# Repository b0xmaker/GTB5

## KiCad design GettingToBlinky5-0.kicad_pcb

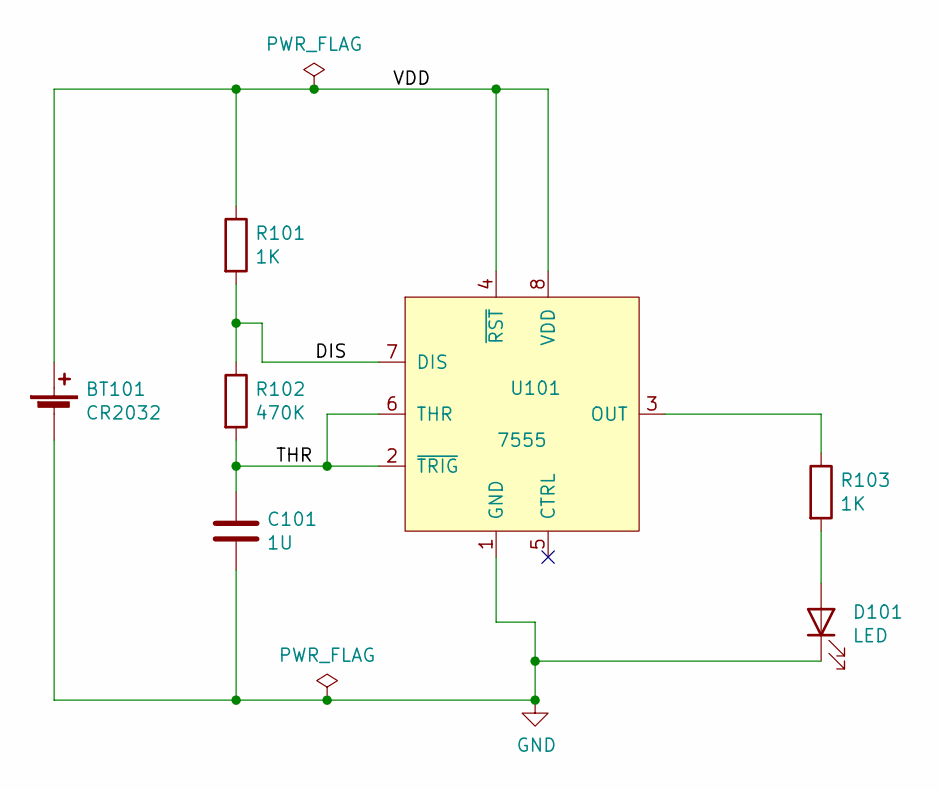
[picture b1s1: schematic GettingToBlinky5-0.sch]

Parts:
BT101: CR2032; S8211-46R
C101: 1U; C_0805_2012Metric_Pad1.15x1.40mm_HandSolder
D101: LED; LED_0805_2012Metric_Pad1.15x1.40mm_HandSolder
R101, R103: 1K; R_0805_2012Metric_Pad1.15x1.40mm_HandSolder
R102: 470K; R_0805_2012Metric_Pad1.15x1.40mm_HandSolder
U101: 7555; SOIC-8_3.9x4.9mm_P1.27mm

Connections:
/DIS: R101.2, R102.1, U101.7 (DIS)
/THR: C101.1, R102.2, U101.2 (~TRIG), U101.6 (THR)
/VDD: BT101.1 (+), R101.1, U101.4 (~RST), U101.8 (VDD)
GND: BT101.2 (-), C101.2, D101.1 (K), U101.1 (GND)
unnamed: D101.2 (A), R103.2
unnamed: R103.1, U101.3 (OUT)

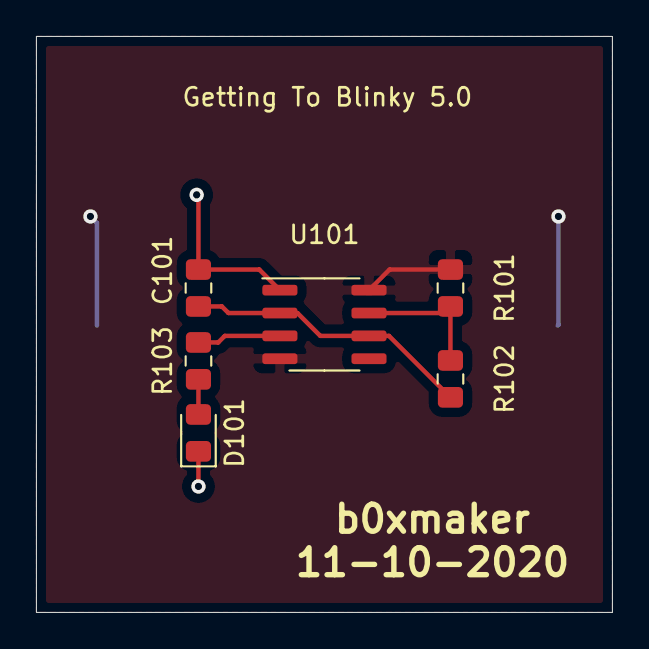
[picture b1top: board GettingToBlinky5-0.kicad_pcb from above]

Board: 2 copper layers, 32.0 x 32.0 mm, 7 parts (1 on the bottom side), 6 nets.
